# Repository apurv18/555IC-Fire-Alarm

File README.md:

# 555IC-Fire-Alarm

This system is built as part of Analog Electronics Course at Birla Institute of Technology and Science. It uses NE555 IC to detect and alert the user of a fire. 
Temperature threshold can be varied by using the potentiometer built into the system. 
On detection of a fire the system sounds a buzzer. 

The system was simulated using LTSpice. Fire stimulus was given as a varying resistance value, as real life implementation uses a thermistor (NTC). 

PCB design was completed in KiCAD IDE.

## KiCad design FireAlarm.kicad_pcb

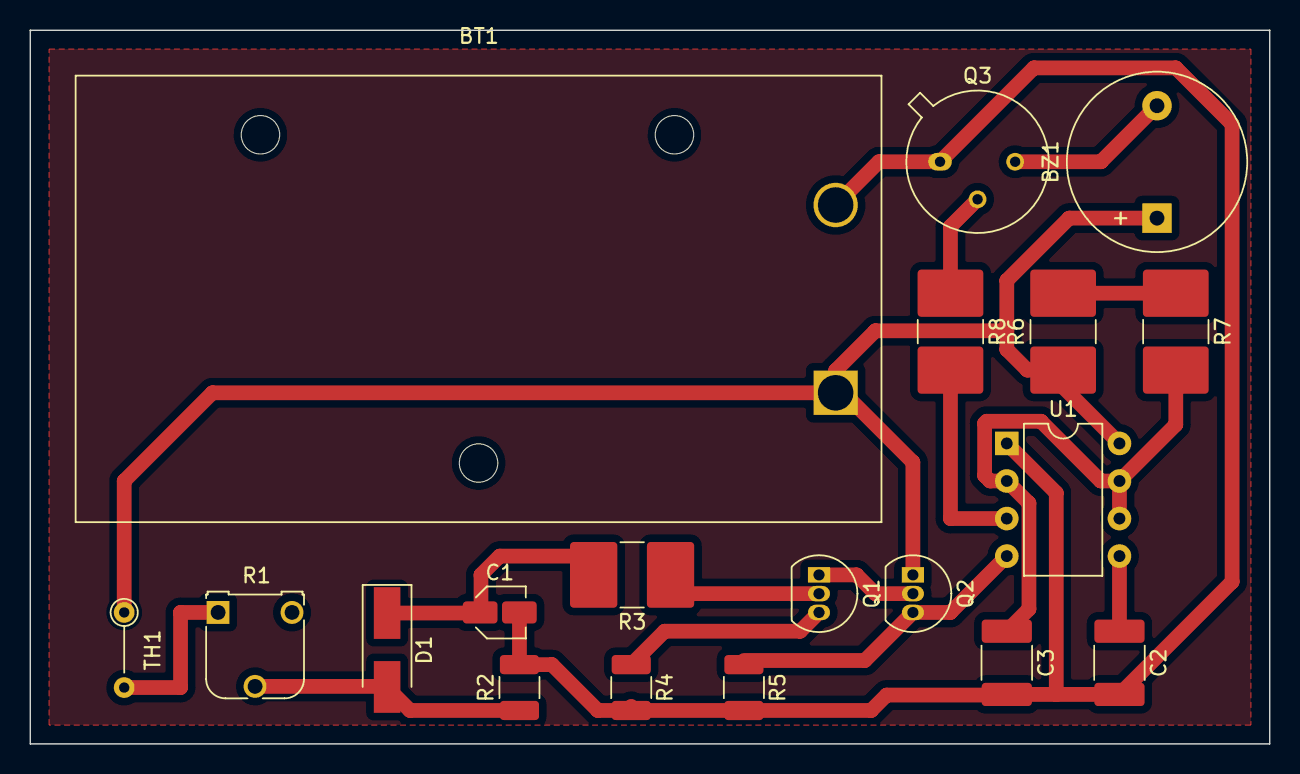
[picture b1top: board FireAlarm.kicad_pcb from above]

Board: 2 copper layers, 83.8 x 48.3 mm, 19 parts (0 on the bottom side), 15 nets.

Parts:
BT1: Battery; BatteryHolder_Eagle_12BH611-GR
BZ1: Buzzer; Buzzer_12x9.5RM7.6
C1: 10U; C_Elec_3x5.4
C2: 0.01U; C_1812_4532Metric_Pad1.57x3.40mm_HandSolder
C3: 0.04U; C_1812_4532Metric_Pad1.57x3.40mm_HandSolder
D1: D; D_SMA_Handsoldering
Q1: BC547; TO-92_Inline
Q2: BC557; TO-92_Inline
Q3: BC141; TO-39-3
R1: R_Variable_US; Potentiometer_Runtron_RM-065_Vertical
R2: 10K_R; R_1210_3225Metric_Pad1.30x2.65mm_HandSolder
R3: 10K_R; R_2816_7142Metric_Pad3.20x4.45mm_HandSolder
R4: 33K_R; R_1210_3225Metric_Pad1.30x2.65mm_HandSolder
R5: 470_R; R_1210_3225Metric_Pad1.30x2.65mm_HandSolder
R6: 47K_R; R_2816_7142Metric_Pad3.20x4.45mm_HandSolder
R7: 560_R; R_2816_7142Metric_Pad3.20x4.45mm_HandSolder
R8: 2.2K_R; R_2816_7142Metric_Pad3.20x4.45mm_HandSolder
TH1: Thermistor_US; R_Axial_DIN0204_L3.6mm_D1.6mm_P5.08mm_Vertical
U1: NE555P; DIP-8_W7.62mm

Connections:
unnamed: BT1.1, BZ1.1, Q2.1, R6.1, TH1.1, U1.8
unnamed: BT1.2, C1.2, C2.2, C3.2, Q3.1, R2.2, R4.2, R5.2, U1.1
unnamed: BZ1.2, Q3.3
unnamed: C1.1, D1.1, R3.2
unnamed: C2.1, U1.5
unnamed: C3.1, R7.2, U1.2, U1.6, U1.7
unnamed: D1.2, R1.2, R2.1
unnamed: Q1.1, Q2.2
unnamed: Q1.2, R3.1
unnamed: Q1.3, R4.1
unnamed: Q2.3, R5.1, U1.4
unnamed: Q3.2, R8.1
unnamed: R1.1, TH1.2
unnamed: R6.2, R7.1
unnamed: R8.2, U1.3
